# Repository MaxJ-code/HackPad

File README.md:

# PhotoPad
PhotoPad is a 12 key macropad with a rotary encoder and an OLED Display, designed to be the best helping hand possible for photography and every other daily-life computer based task.

It's supposed to help speeding up the Lightroom Classic workflow, aswell as basic navigation.
The firmware isn't final, because I don't know the keylayout that fits me best, yet.

# Design

# Schematic

# PCB

# Case
It features two separate parts with a support for the screen, the cutout for the USB-C and standoffs for the PCB.

# Firmware
The firmware is KMK based and easy to understand.

# BOM
- 1x Case (2 3D-printed parts)
- 1x XIAO RP2040
- 11x Cherry MX Switches
- 1x EC11 Rotary Encoder
- 1x 0.91" 128x32 OLED Display
- 12x 1N4148 DO-35 Diodes.
- 4x M3x5x4 Heatset inserts
- 4X M3x12mm SHCS Bolts

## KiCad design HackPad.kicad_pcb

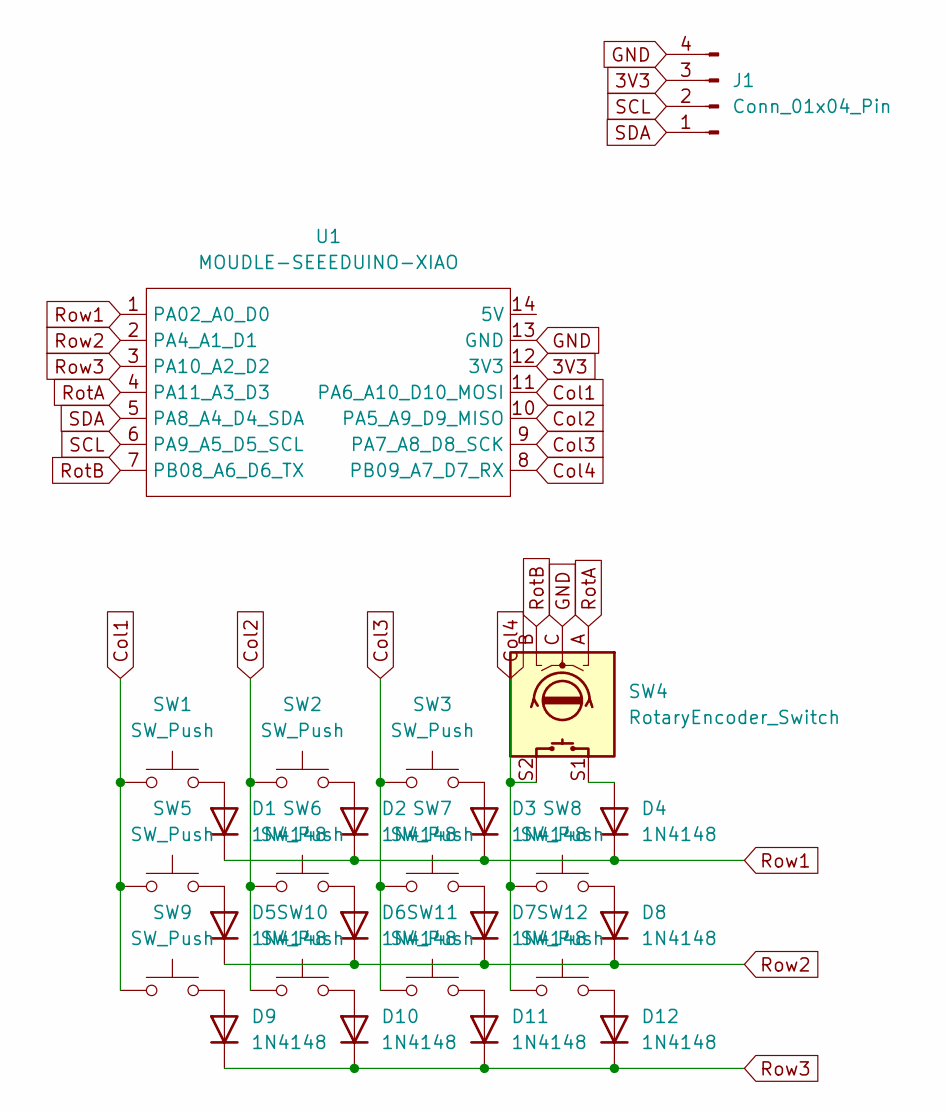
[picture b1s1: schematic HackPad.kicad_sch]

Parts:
D1, D2, D3, D4, D5, D6, D7, D8, D9, D10, D11, D12: 1N4148; D_DO-35_SOD27_P7.62mm_Horizontal
J1: Conn_01x04_Pin; PinSocket_1x04_P2.54mm_Vertical
SW1, SW2, SW3, SW5, SW6, SW7, SW8, SW9, SW10, SW11, SW12: SW_Push; SW_Cherry_MX_1.00u_PCB
SW4: RotaryEncoder_Switch; RotaryEncoder_Alps_EC11E-Switch_Vertical_H20mm
U1: MOUDLE-SEEEDUINO-XIAO; XIAO-Generic-Hybrid-14P-2.54-21X17.8MM

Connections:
3V3: J1.3, U1.12 (3V3)
Col1: SW1.1, SW5.1, SW9.1, U1.11 (PA6_A10_D10_MOSI)
Col2: SW2.1, SW6.1, SW10.1, U1.10 (PA5_A9_D9_MISO)
Col3: SW3.1, SW7.1, SW11.1, U1.9 (PA7_A8_D8_SCK)
Col4: SW4.S2, SW8.1, SW12.1, U1.8 (PB09_A7_D7_RX)
GND: J1.4, SW4.C, U1.13 (GND)
unnamed: D1.2 (A), SW1.2
unnamed: D2.2 (A), SW2.2
unnamed: D3.2 (A), SW3.2
unnamed: D4.2 (A), SW4.S1
unnamed: D5.2 (A), SW5.2
unnamed: D6.2 (A), SW6.2
unnamed: D7.2 (A), SW7.2
unnamed: D8.2 (A), SW8.2
unnamed: D9.2 (A), SW9.2
unnamed: D10.2 (A), SW10.2
unnamed: D11.2 (A), SW11.2
unnamed: D12.2 (A), SW12.2
RotA: SW4.A, U1.4 (PA11_A3_D3)
RotB: SW4.B, U1.7 (PB08_A6_D6_TX)
Row1: D1.1 (K), D2.1 (K), D3.1 (K), D4.1 (K), U1.1 (PA02_A0_D0)
Row2: D5.1 (K), D6.1 (K), D7.1 (K), D8.1 (K), U1.2 (PA4_A1_D1)
Row3: D9.1 (K), D10.1 (K), D11.1 (K), D12.1 (K), U1.3 (PA10_A2_D2)
SCL: J1.2, U1.6 (PA9_A5_D5_SCL)
SDA: J1.1, U1.5 (PA8_A4_D4_SDA)

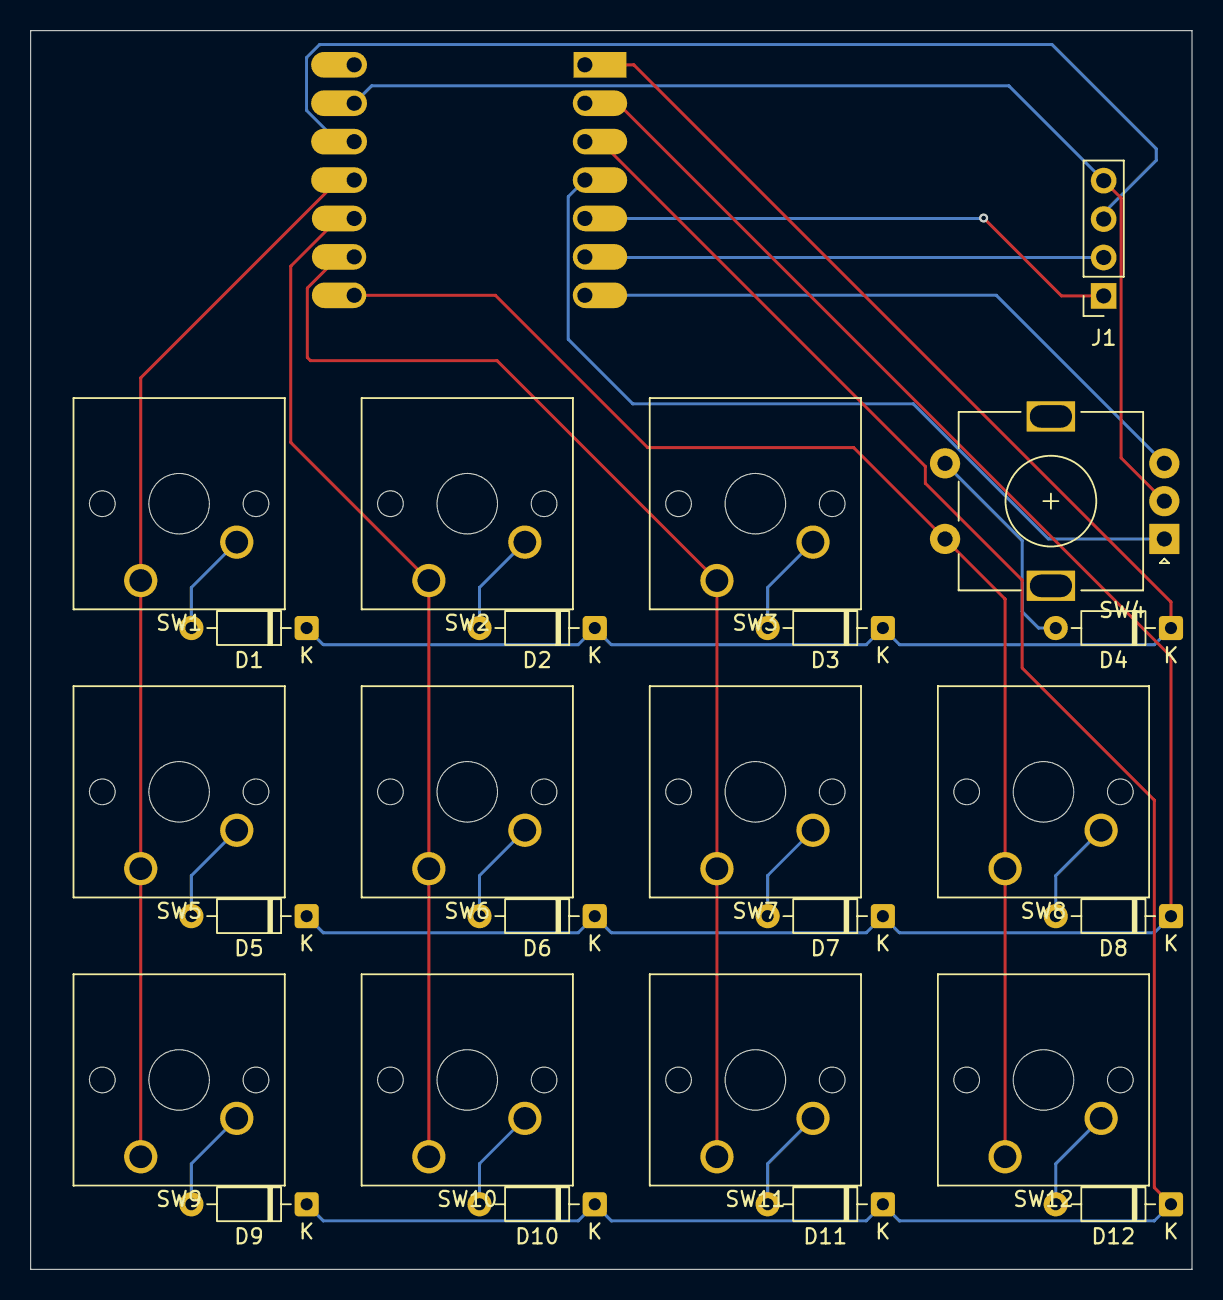
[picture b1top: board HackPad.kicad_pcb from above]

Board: 2 copper layers, 76.8 x 81.9 mm, 26 parts (1 on the bottom side), 25 nets.

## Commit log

2026-06-10 Revise README for PhotoPad project details
    Updated project name and added detailed descriptions for the PhotoPad, including design, schematic, PCB, case, firmware, and BOM sections.
2026-06-10 Add images to README for case views
    Added images for case side and back views.
2026-06-10 Fix duplicate BOM entries in README
    Removed duplicate BOM entries in the README.
